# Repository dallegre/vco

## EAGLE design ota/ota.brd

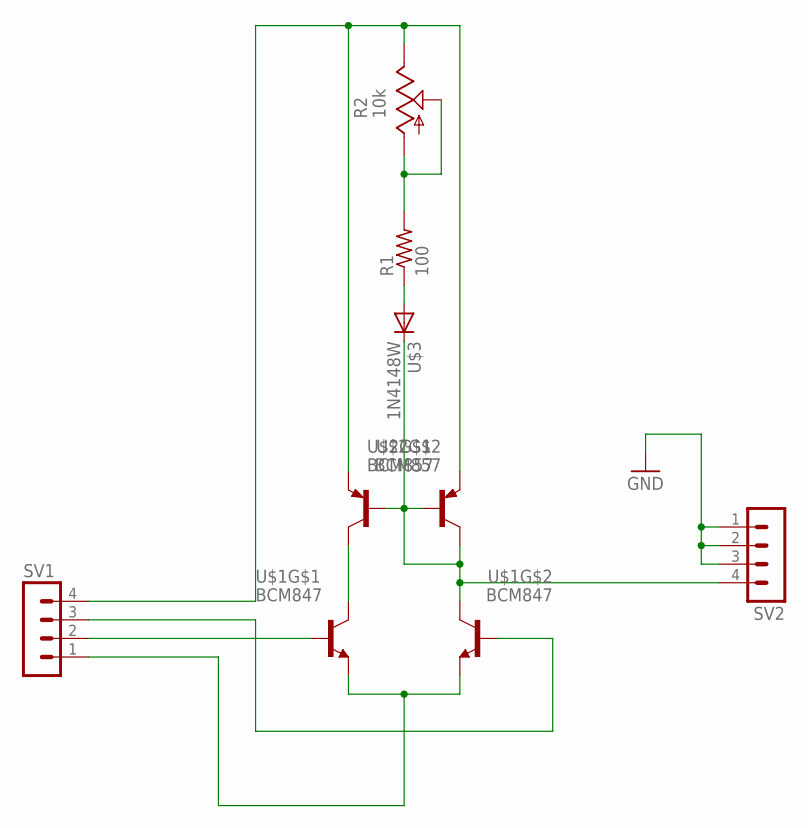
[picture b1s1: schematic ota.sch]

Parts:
R1: 100; R0603
R2: 10k; SM-42/43W
SV1, SV2: MA04-1
U$1: BCM847; SOT457R_PHILIPS
U$2: BCM857; SOT457R_PHILIPS
U$3: 1N4148W; SOD123

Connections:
GND: SV2.1, SV2.2, SV2.3
unnamed: SV1.1, U$1.1 (E), U$1.4 (E)
unnamed: U$1.6 (C), U$2.3 (C)
unnamed: R1.2, R2.1 (A), R2.2 (S)
unnamed: R2.3 (E), SV1.4, U$2.1 (E), U$2.4 (E)
unnamed: SV2.4, U$1.3 (C), U$2.2 (B), U$2.5 (B), U$2.6 (C), U$3.C
unnamed: R1.1, U$3.A
unnamed: SV1.3, U$1.5 (B)
unnamed: SV1.2, U$1.2 (B)

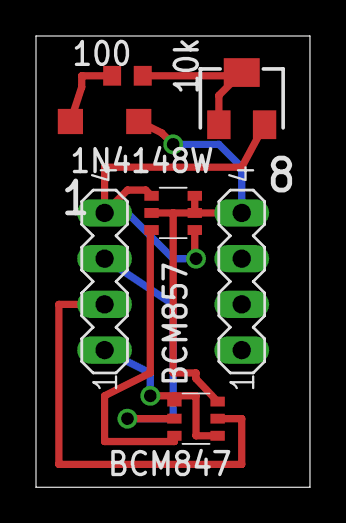
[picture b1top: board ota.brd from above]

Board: 2 copper layers, 15.2 x 25.1 mm, 7 parts (0 on the bottom side), 9 nets.

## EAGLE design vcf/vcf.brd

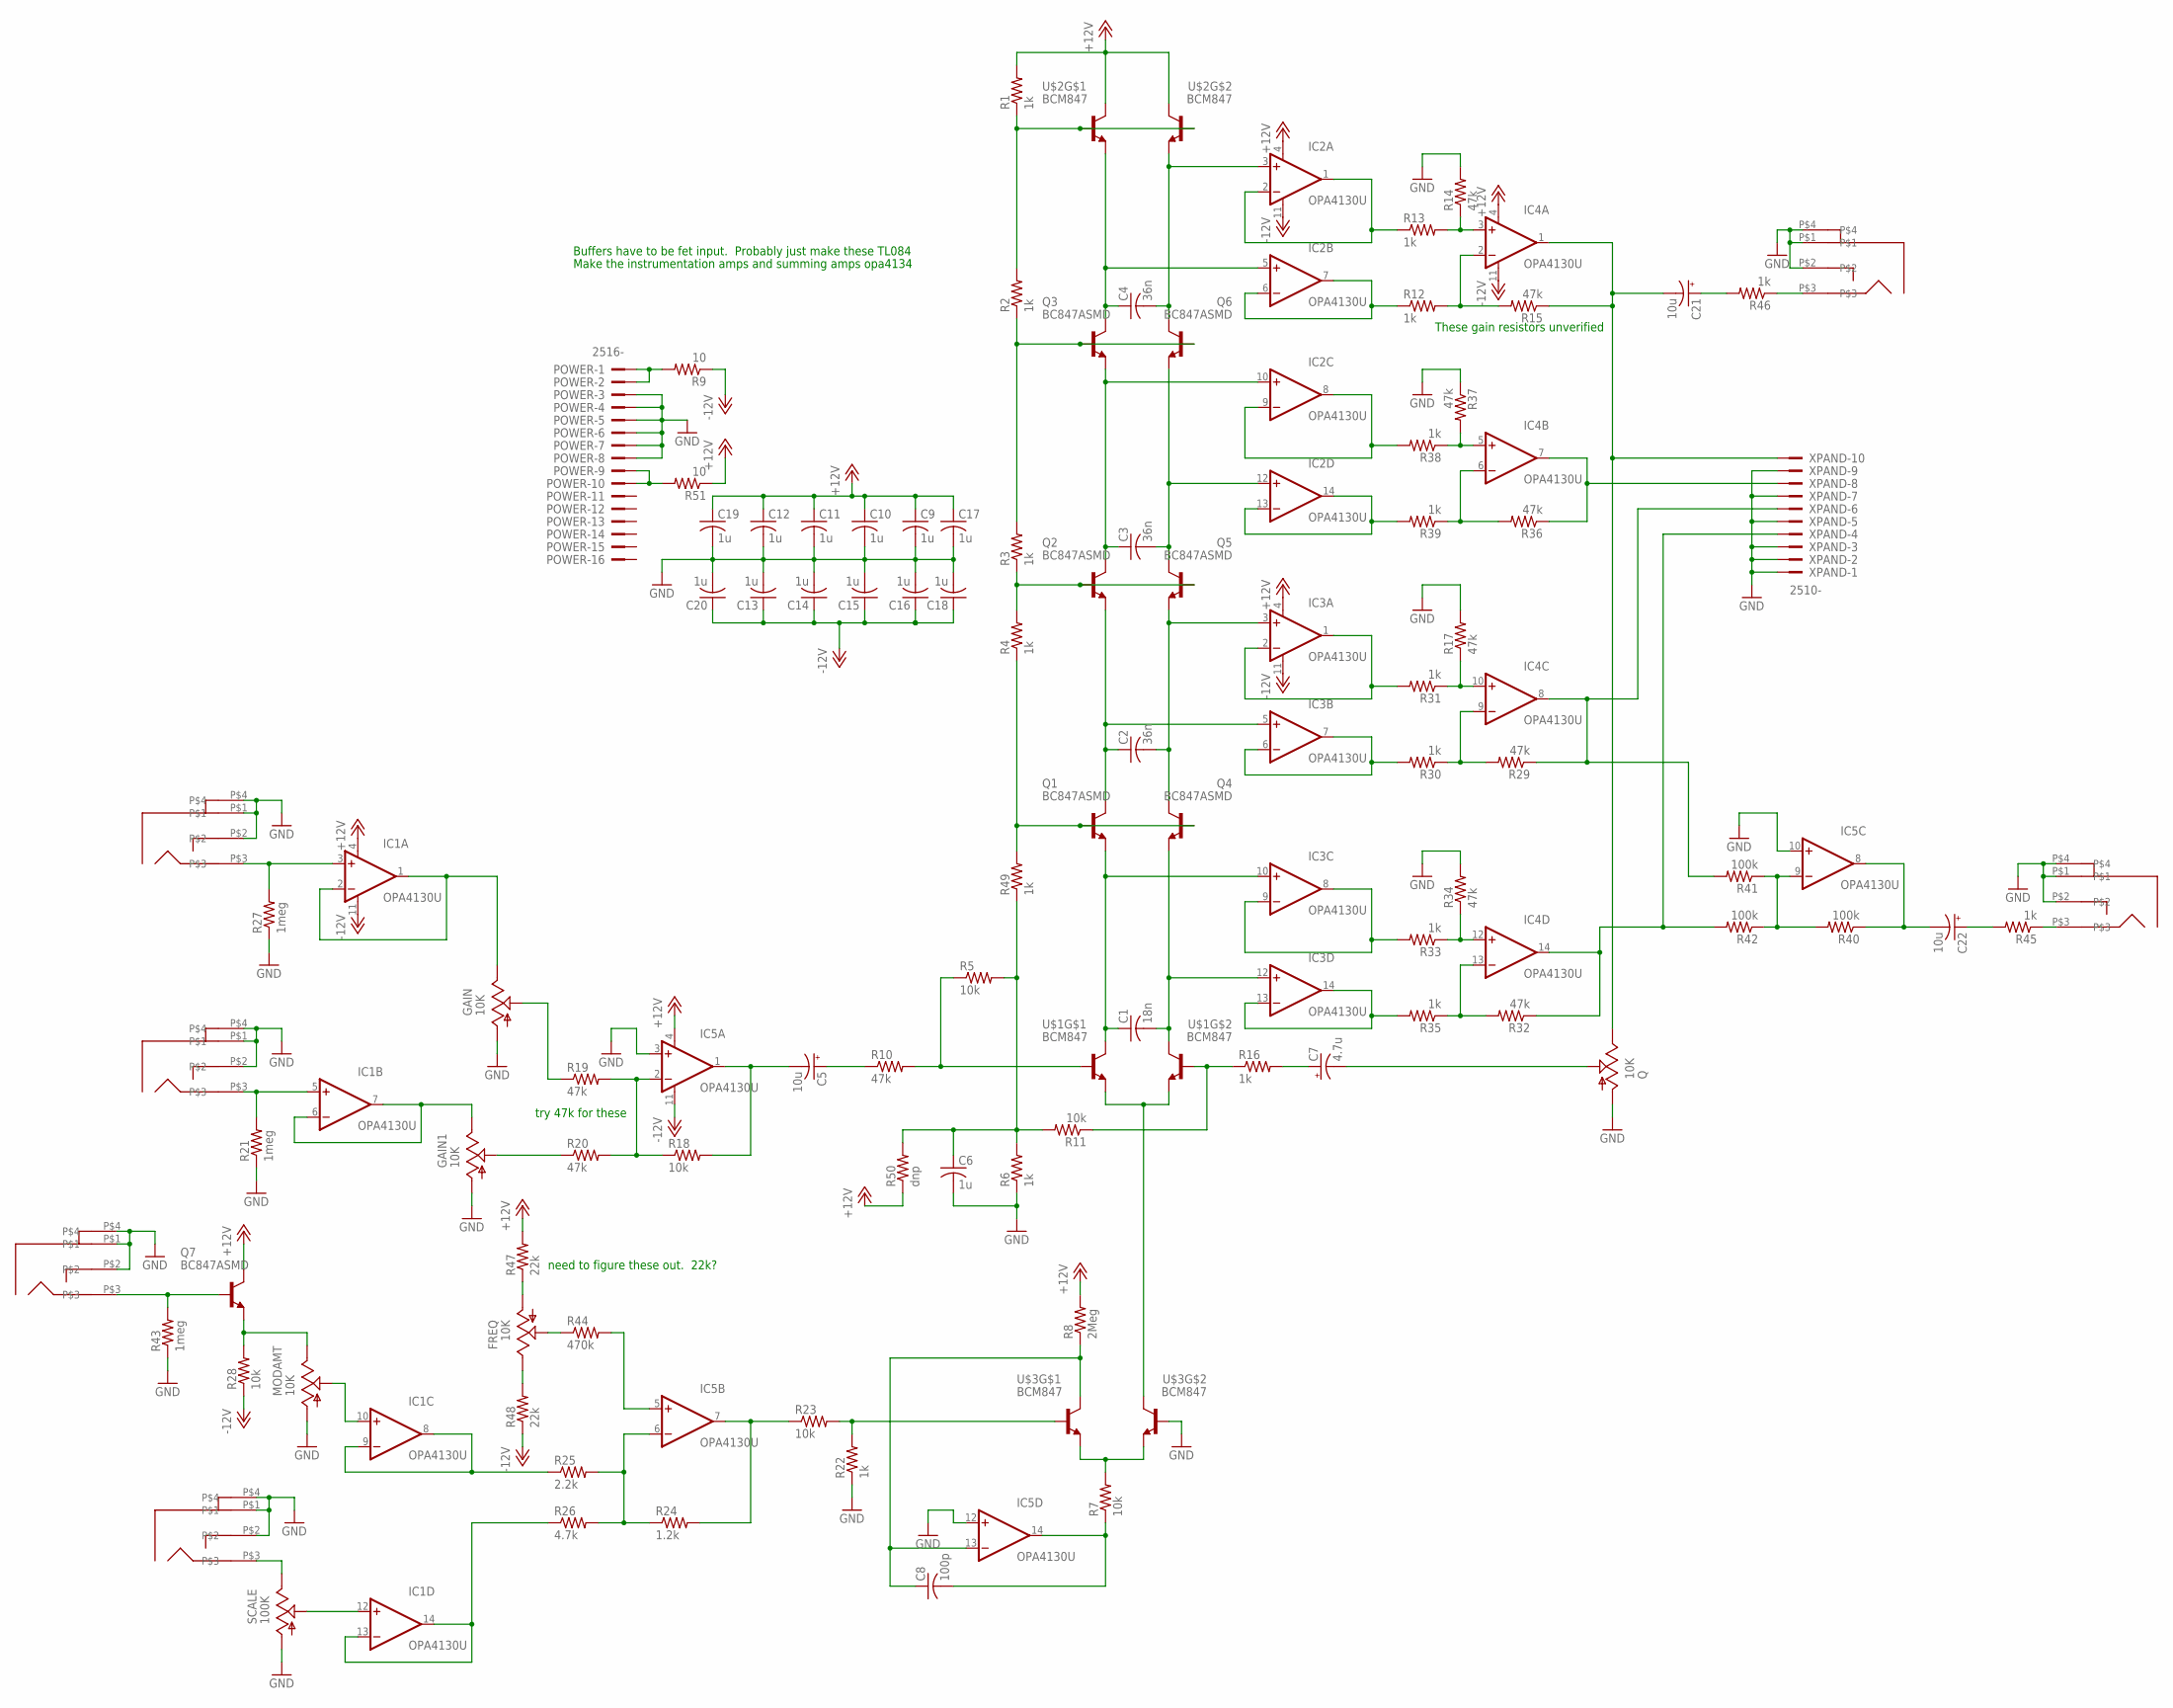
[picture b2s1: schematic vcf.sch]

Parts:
AIN, AIN2: PJ301BM
BP: PJ301BM
C1: 18n; C0603
C2, C3, C4: 36n; C0603
C5, C21, C22: 10u; E2,5-6
C6, C9, C10, C11, C12, C13, C14, C15, C16, C17, C18, C19, C20: 1u; C0603
C7: 4.7u; E2,5-6
C8: 100p; C0603
FREQ: 10K; EVUFXJ
GAIN, GAIN1: 10K; EVUFXJ
IC1, IC2, IC3, IC4, IC5: OPA4130U; SO14
LP: PJ301BM
MIN: PJ301BM
MODAMT: 10K; EVUFXJ
POWER: 2516-; PAK100/2500-16
Q: 10K; EVUFXJ
Q1, Q2, Q3, Q4, Q5, Q6, Q7: BC847ASMD; SOT23
R1, R2, R3, R4, R6, R12, R13, R16, R22, R30, R31, R33, R35, R38, R39, R45, R46, R49: 1k; R0603
R5, R7, R11, R18, R23, R28: 10k; R0603
R8: 2Meg; R0603
R9, R51: 10; R0603
R10, R14, R15, R17, R19, R20, R29, R32, R34, R36, R37: 47k; R0603
R21, R27, R43: 1meg; R0603
R24: 1.2k; R0603
R25: 2.2k; R0603
R26: 4.7k; R0603
R40, R41, R42: 100k; R0603
R44: 470k; R0603
R47, R48: 22k; R0603
R50: dnp; R0603
SCALE: 100K; S64W
U$1, U$2, U$3: BCM847; SOT457R_PHILIPS
VPEROCT: PJ301BM
XPAND: 2510-; PAK100/2500-10

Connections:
+12V: C9.1, C10.1, C11.1, C12.1, C17.1, C19.1, IC1.4 (V+), IC2.4 (V+), IC3.4 (V+), IC4.4 (V+), IC5.4 (V+), Q7.3 (C), R1.2, R8.2, R47.2, R50.1, R51.1, U$2.3 (C), U$2.6 (C)
-12V: C13.1, C14.1, C15.1, C16.1, C18.1, C20.1, IC1.11 (V-), IC2.11 (V-), IC3.11 (V-), IC4.11 (V-), IC5.11 (V-), R9.1, R28.1, R48.1
GND: AIN.P$1, AIN.P$2, AIN.P$4, AIN2.P$1, AIN2.P$2, AIN2.P$4, BP.P$1, BP.P$2, BP.P$4, C6.2, C9.2, C10.2, C11.2, C12.2, C13.2, C14.2, C15.2, C16.2, C17.2, C18.2, C19.2, C20.2, GAIN.1 (A), GAIN1.1 (A), IC5.3 (+IN), IC5.10 (+IN), IC5.12 (+IN), LP.P$1, LP.P$2, LP.P$4, MIN.P$1, MIN.P$2, MIN.P$4, MODAMT.1 (A), POWER.3, POWER.4, POWER.5, POWER.6, POWER.7, POWER.8, Q.1 (A), R6.1, R14.2, R17.2, R21.1, R22.1, R27.1, R34.2, R37.1, R43.1, SCALE.A, U$3.5 (B), VPEROCT.P$1, VPEROCT.P$2, VPEROCT.P$4, XPAND.1, XPAND.2, XPAND.3, XPAND.5, XPAND.7, XPAND.9
unnamed: U$1.1 (E), U$1.4 (E), U$3.3 (C)
unnamed: C1.1, IC3.10 (+IN), Q1.2 (E), U$1.6 (C)
unnamed: C2.1, IC3.5 (+IN), Q1.3 (C), Q2.2 (E)
unnamed: C3.1, IC2.10 (+IN), Q2.3 (C), Q3.2 (E)
unnamed: C3.2, IC2.12 (+IN), Q5.3 (C), Q6.2 (E)
unnamed: C2.2, IC3.3 (+IN), Q4.3 (C), Q5.2 (E)
unnamed: C1.2, IC3.12 (+IN), Q4.2 (E), U$1.3 (C)
unnamed: C4.2, IC2.3 (+IN), Q6.3 (C), U$2.4 (E)
unnamed: C4.1, IC2.5 (+IN), Q3.3 (C), U$2.1 (E)
unnamed: R1.1, R2.2, U$2.2 (B), U$2.5 (B)
unnamed: Q3.1 (B), Q6.1 (B), R2.1, R3.2
unnamed: Q2.1 (B), Q5.1 (B), R3.1, R4.2
unnamed: Q1.1 (B), Q4.1 (B), R4.1, R49.2
unnamed: R5.1, R10.2, U$1.2 (B)
unnamed: IC5.2 (-IN), R18.1, R19.2, R20.2
unnamed: R7.2, U$3.1 (E), U$3.4 (E)
unnamed: C8.2, IC5.14 (OUT), R7.1
unnamed: MIN.P$3, Q7.1 (B), R43.2
unnamed: C8.1, IC5.13 (-IN), R8.1, U$3.6 (C)
unnamed: C5.-, IC5.1 (OUT), R18.2
unnamed: C5.+, R10.1
unnamed: R11.1, R16.1, U$1.5 (B)
unnamed: IC2.1 (OUT), IC2.2 (-IN), R13.1
unnamed: IC5.5 (+IN), R44.2
unnamed: IC4.2 (-IN), R12.2, R15.2
unnamed: IC4.3 (+IN), R13.2, R14.1
unnamed: C21.-, IC4.1 (OUT), Q.3 (E), R15.1, XPAND.10
unnamed: IC2.8 (OUT), IC2.9 (-IN), R38.2
unnamed: IC1.8 (OUT), IC1.9 (-IN), R25.1
unnamed: GAIN1.3 (E), IC1.6 (-IN), IC1.7 (OUT)
unnamed: C7.+, R16.2
unnamed: C7.-, Q.2 (S)
unnamed: MODAMT.3 (E), Q7.2 (E), R28.2
unnamed: R22.2, R23.2, U$3.2 (B)
unnamed: IC2.6 (-IN), IC2.7 (OUT), R12.1
unnamed: IC5.6 (-IN), R24.1, R25.2, R26.2
unnamed: IC3.1 (OUT), IC3.2 (-IN), R31.2
unnamed: IC1.13 (-IN), IC1.14 (OUT), R26.1
unnamed: IC3.8 (OUT), IC3.9 (-IN), R33.2
unnamed: SCALE.E, VPEROCT.P$3
unnamed: IC1.12 (+IN), SCALE.S
unnamed: IC2.13 (-IN), IC2.14 (OUT), R39.2
unnamed: GAIN.2 (S), R19.1
unnamed: IC3.6 (-IN), IC3.7 (OUT), R30.2
unnamed: IC4.10 (+IN), R17.1, R31.1
unnamed: IC4.9 (-IN), R29.2, R30.1
unnamed: IC4.8 (OUT), R29.1, R41.2, XPAND.6
unnamed: IC3.13 (-IN), IC3.14 (OUT), R35.2
unnamed: BP.P$3, R45.1
unnamed: IC1.10 (+IN), MODAMT.2 (S)
unnamed: IC4.13 (-IN), R32.2, R35.1
unnamed: IC4.14 (OUT), R32.1, R42.2, XPAND.4
unnamed: IC5.7 (OUT), R23.1, R24.2
unnamed: IC4.12 (+IN), R33.1, R34.1
unnamed: IC4.5 (+IN), R37.2, R38.1
unnamed: IC4.6 (-IN), R36.2, R39.1
unnamed: GAIN1.2 (S), R20.1
unnamed: IC4.7 (OUT), R36.1, XPAND.8
unnamed: IC5.9 (-IN), R40.2, R41.1, R42.1
unnamed: FREQ.1 (A), R47.1
unnamed: C22.-, IC5.8 (OUT), R40.1
unnamed: AIN.P$3, IC1.3 (+IN), R27.2
unnamed: C21.+, R46.2
unnamed: LP.P$3, R46.1
unnamed: FREQ.2 (S), R44.1
unnamed: FREQ.3 (E), R48.2
unnamed: GAIN.3 (E), IC1.1 (OUT), IC1.2 (-IN)
unnamed: C6.1, R5.2, R6.2, R11.2, R49.1, R50.2
unnamed: AIN2.P$3, IC1.5 (+IN), R21.2
unnamed: C22.+, R45.2
unnamed: POWER.9, POWER.10, R51.2
unnamed: POWER.1, POWER.2, R9.2

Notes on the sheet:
Buffers have to be fet input. Probably just make these TL084
need to figure these out. 22k?
try 47k for these
These gain resistors unverified
Make the instrumentation amps and summing amps opa4134

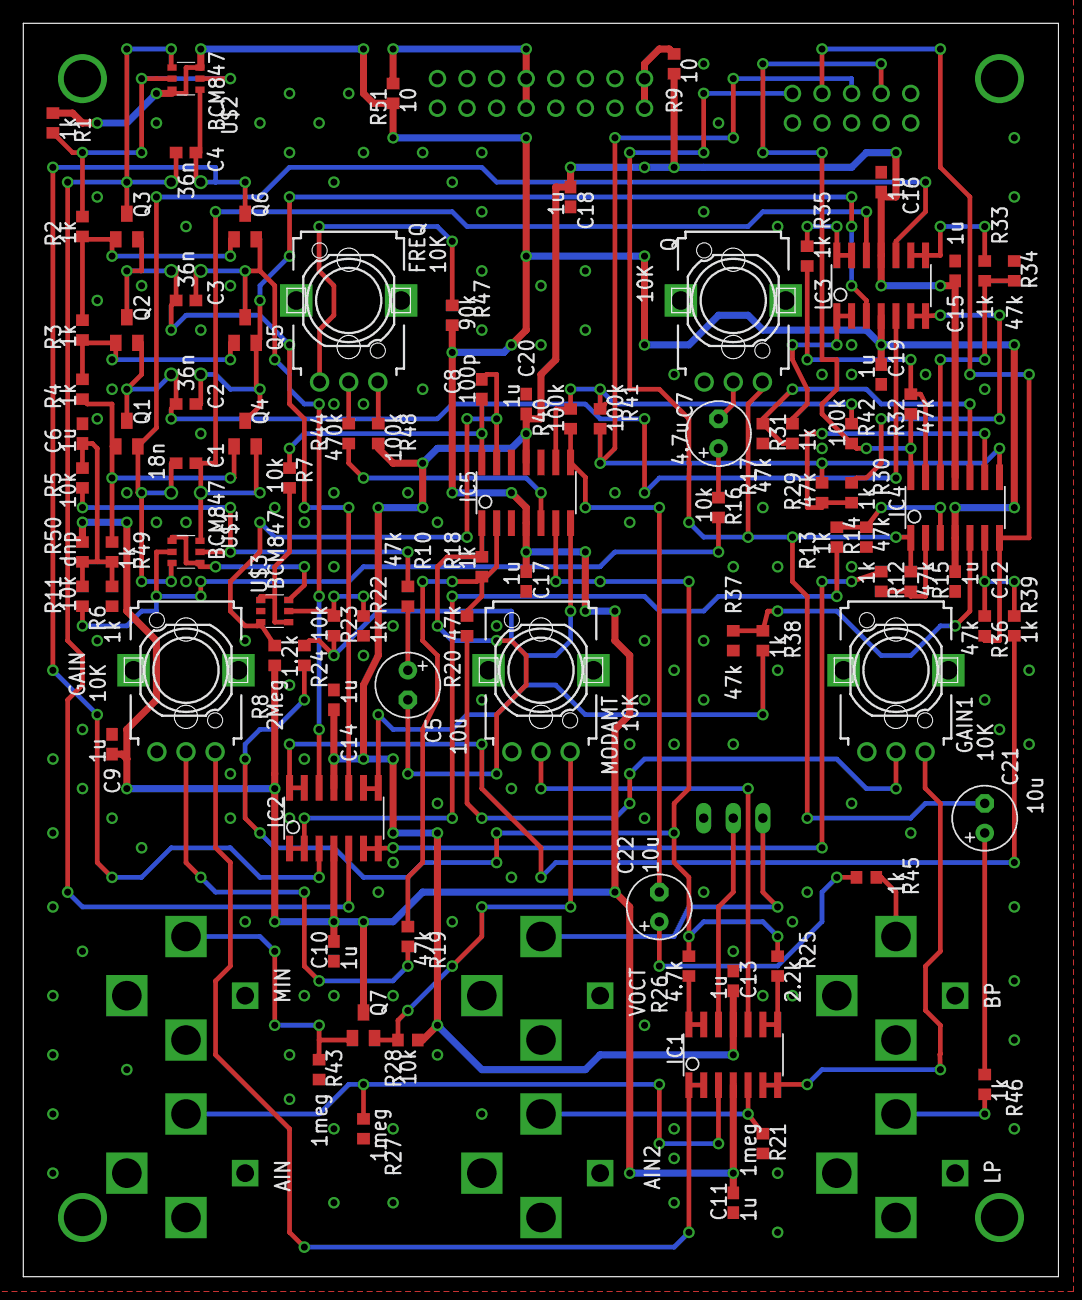
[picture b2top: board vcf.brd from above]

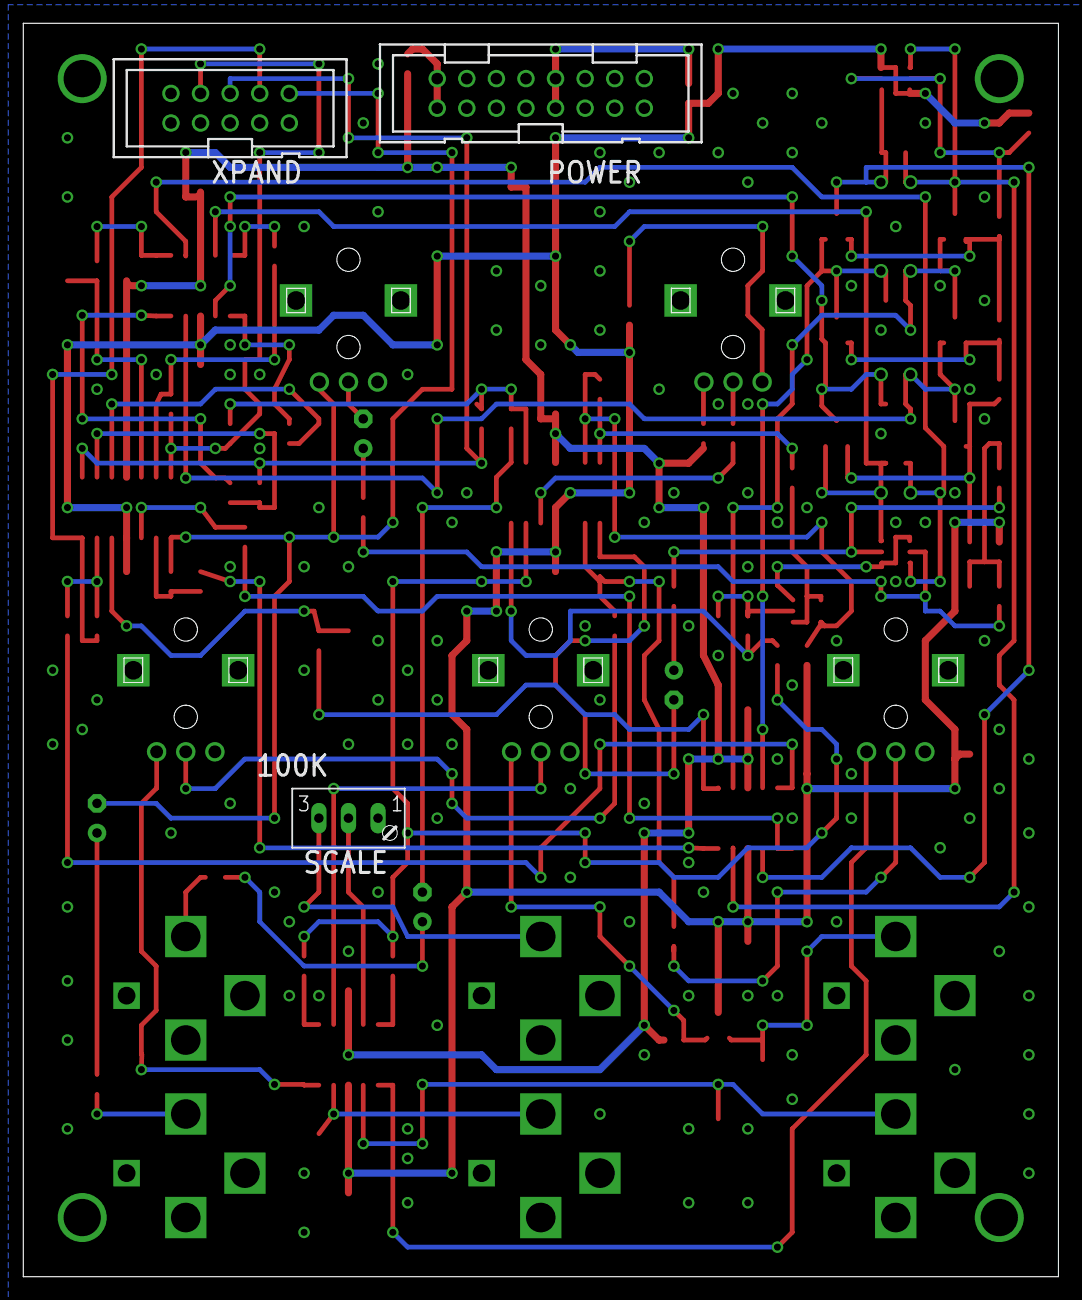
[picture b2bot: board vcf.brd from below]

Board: 2 copper layers, 88.9 x 107.6 mm, 102 parts (3 on the bottom side), 75 nets.
